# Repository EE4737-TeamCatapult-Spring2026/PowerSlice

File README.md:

# PowerSlice
The slice that does the power stuff

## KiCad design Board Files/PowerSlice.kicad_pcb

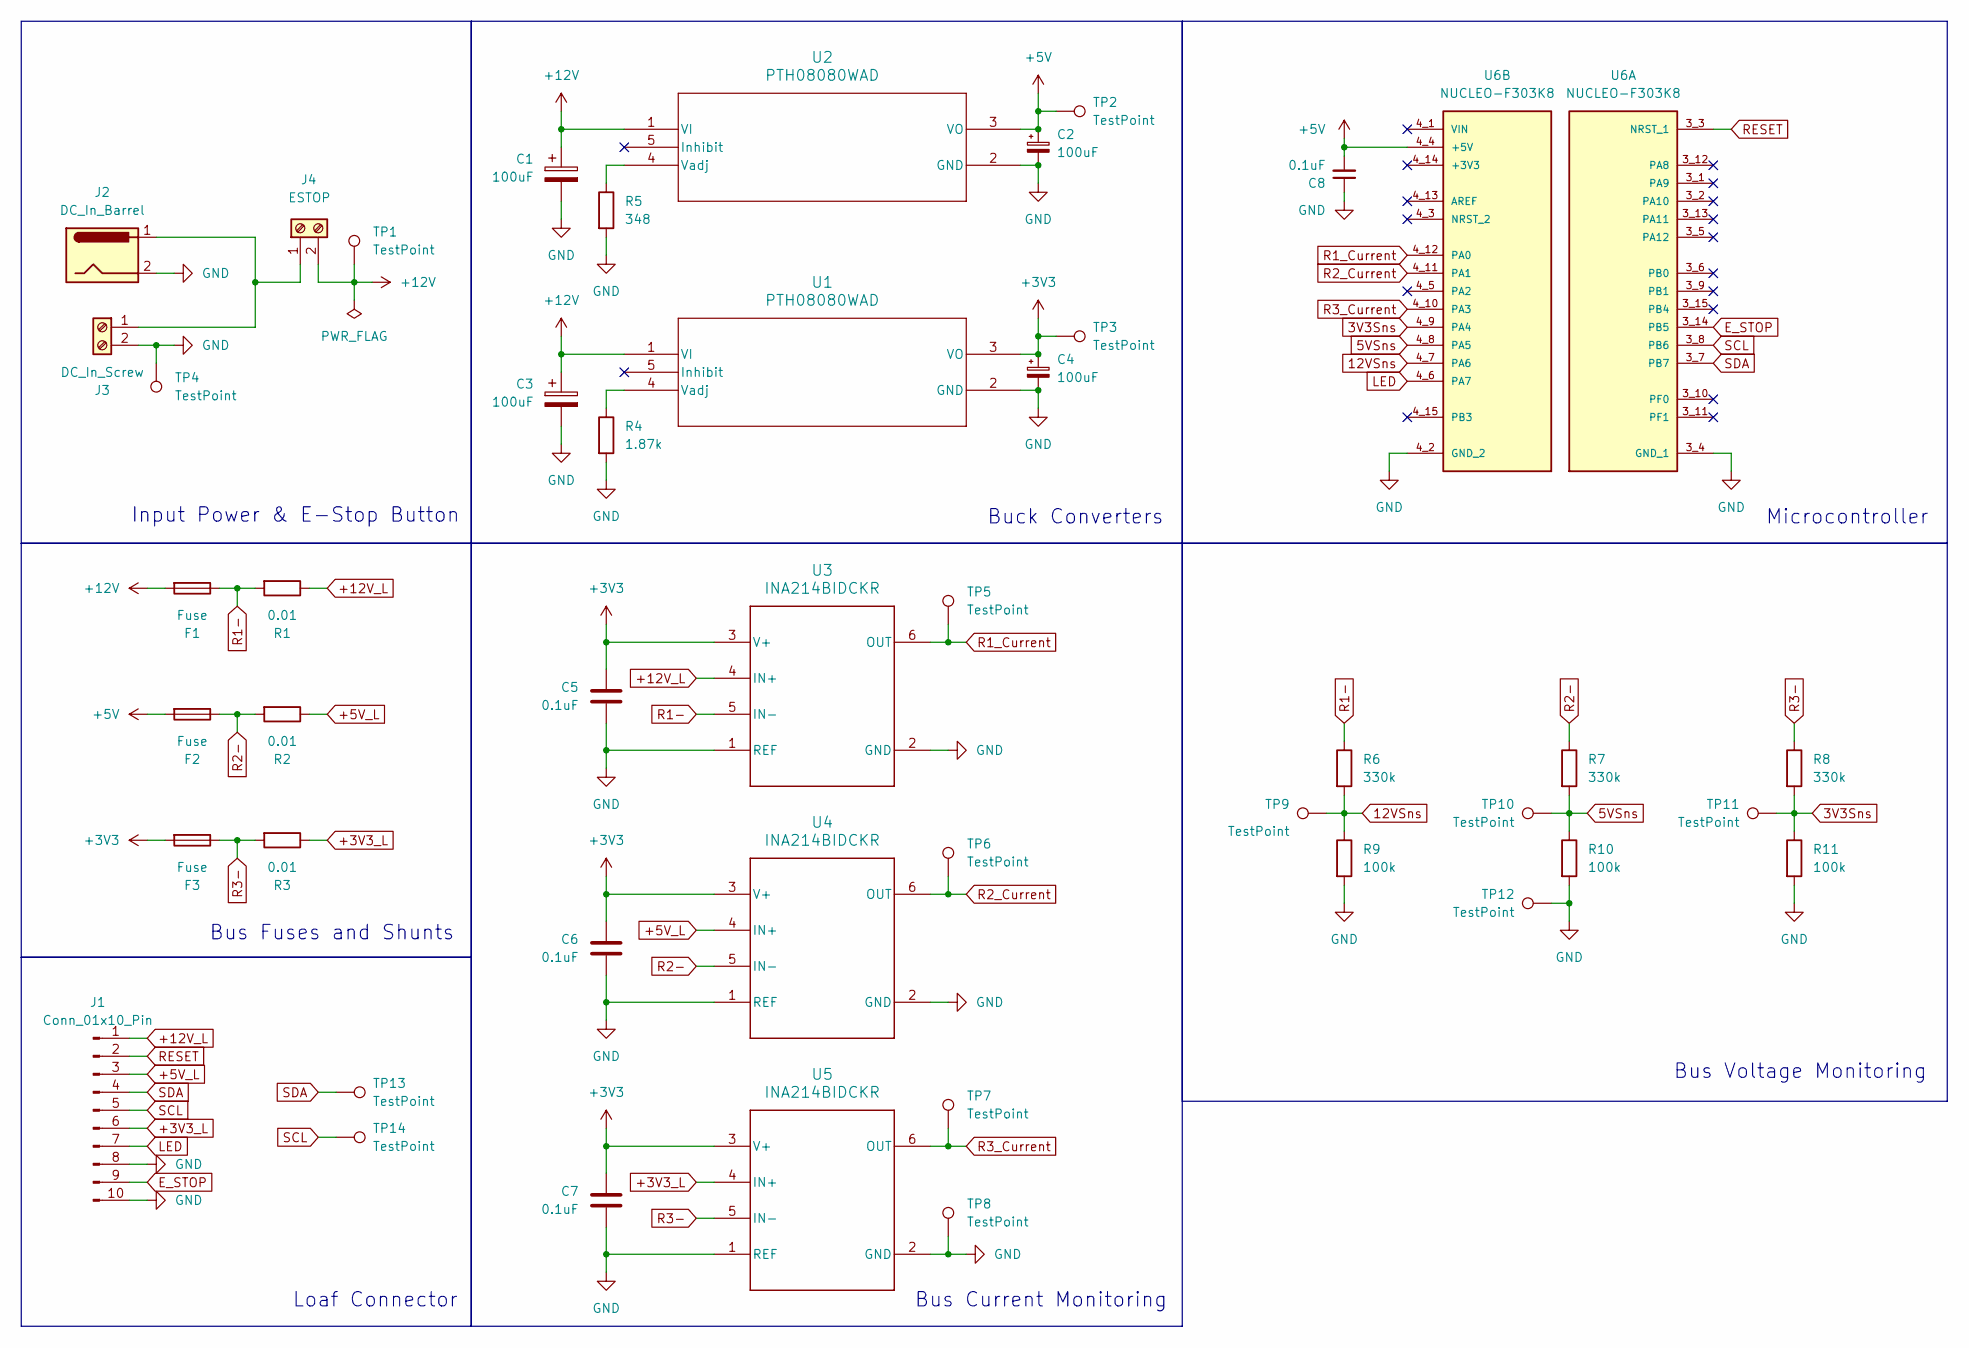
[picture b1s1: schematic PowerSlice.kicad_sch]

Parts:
C1, C2, C3, C4: 100uF; CP_Radial_D6.3mm_P2.50mm
C5, C6, C7, C8: 0.1uF; C_1206_3216Metric_Pad1.33x1.80mm_HandSolder
F1, F2, F3: Fuse; FUSE_354 101-GY_LTF
J1: Conn_01x10_Pin; PinHeader_1x10_P2.54mm_Horizontal
J2: DC_In_Barrel
J3: DC_In_Screw; 691137710002
J4: ESTOP; 691137710002
R1, R2, R3: 0.01; R_1206_3216Metric_Pad1.30x1.75mm_HandSolder
R4: 1.87k; R_1206_3216Metric_Pad1.30x1.75mm_HandSolder
R5: 348; R_1206_3216Metric_Pad1.30x1.75mm_HandSolder
R6, R7, R8: 330k; R_1206_3216Metric_Pad1.30x1.75mm_HandSolder
R9, R10, R11: 100k; R_1206_3216Metric_Pad1.30x1.75mm_HandSolder
TP1, TP2, TP3, TP4, TP5, TP6, TP7, TP8, TP9, TP10, TP11, TP12, TP13, TP14: TestPoint; TestPoint_Keystone_5005-5009_Compact
U1, U2: PTH08080WAD; EUF5
U3, U4, U5: INA214BIDCKR; DCK0006A_N
U6: NUCLEO-F303K8; MODULE_NUCLEO-F303K8; PARTREV 5

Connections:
3V3Sns: R8.2, R11.1, TP11.1 (1_1), U6.4_9 (PA4)
5VSns: R7.2, R10.1, TP10.1 (1_1), U6.4_8 (PA5)
12VSns: R6.2, R9.1, TP9.1 (1_1), U6.4_7 (PA6)
+3V3: C4.1, C5.1, C6.1, C7.1, F3.2, TP3.1 (1_1), U1.3 (VO), U3.3 (V+), U4.3 (V+), U5.3 (V+)
+3V3_L: J1.6, R3.1, U5.4 (IN+)
+5V: C2.1, C8.2, F2.2, TP2.1 (1_1), U2.3 (VO), U6.4_4 (+5V)
+5V_L: J1.3, R2.1, U4.4 (IN+)
+12V: C1.1, C3.1, F1.2, J4.2, TP1.1 (1_1), U1.1 (VI), U2.1 (VI)
+12V_L: J1.1, R1.1, U3.4 (IN+)
E_STOP: J1.9, U6.3_14 (PB5)
GND: C1.2, C2.2, C3.2, C4.2, C5.2, C6.2, C7.2, C8.1, J1.8, J1.10, J2.2, J3.2, R4.2, R5.2, R9.2, R10.2, R11.2, TP4.1 (1_1), TP8.1 (1_1), TP12.1 (1_1), U1.2 (GND), U2.2 (GND), U3.1 (REF), U3.2 (GND), U4.1 (REF), U4.2 (GND), U5.1 (REF), U5.2 (GND), U6.3_4 (GND_1), U6.4_2 (GND_2)
LED: J1.7, U6.4_6 (PA7)
unnamed: J2.1, J3.1, J4.1
unnamed: R4.1, U1.4 (Vadj)
unnamed: R5.1, U2.4 (Vadj)
R1-: F1.1, R1.2, R6.1, U3.5 (IN-)
R1_Current: TP5.1 (1_1), U3.6 (OUT), U6.4_12 (PA0)
R2-: F2.1, R2.2, R7.1, U4.5 (IN-)
R2_Current: TP6.1 (1_1), U4.6 (OUT), U6.4_11 (PA1)
R3-: F3.1, R3.2, R8.1, U5.5 (IN-)
R3_Current: TP7.1 (1_1), U5.6 (OUT), U6.4_10 (PA3)
RESET: J1.2, U6.3_3 (NRST_1)
SCL: J1.5, TP14.1 (1_1), U6.3_8 (PB6)
SDA: J1.4, TP13.1 (1_1), U6.3_7 (PB7)

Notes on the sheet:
Microcontroller
Bus Fuses and Shunts
Input Power & E-Stop Button
Bus Voltage Monitoring
Bus Current Monitoring
Loaf Connector
Buck Converters

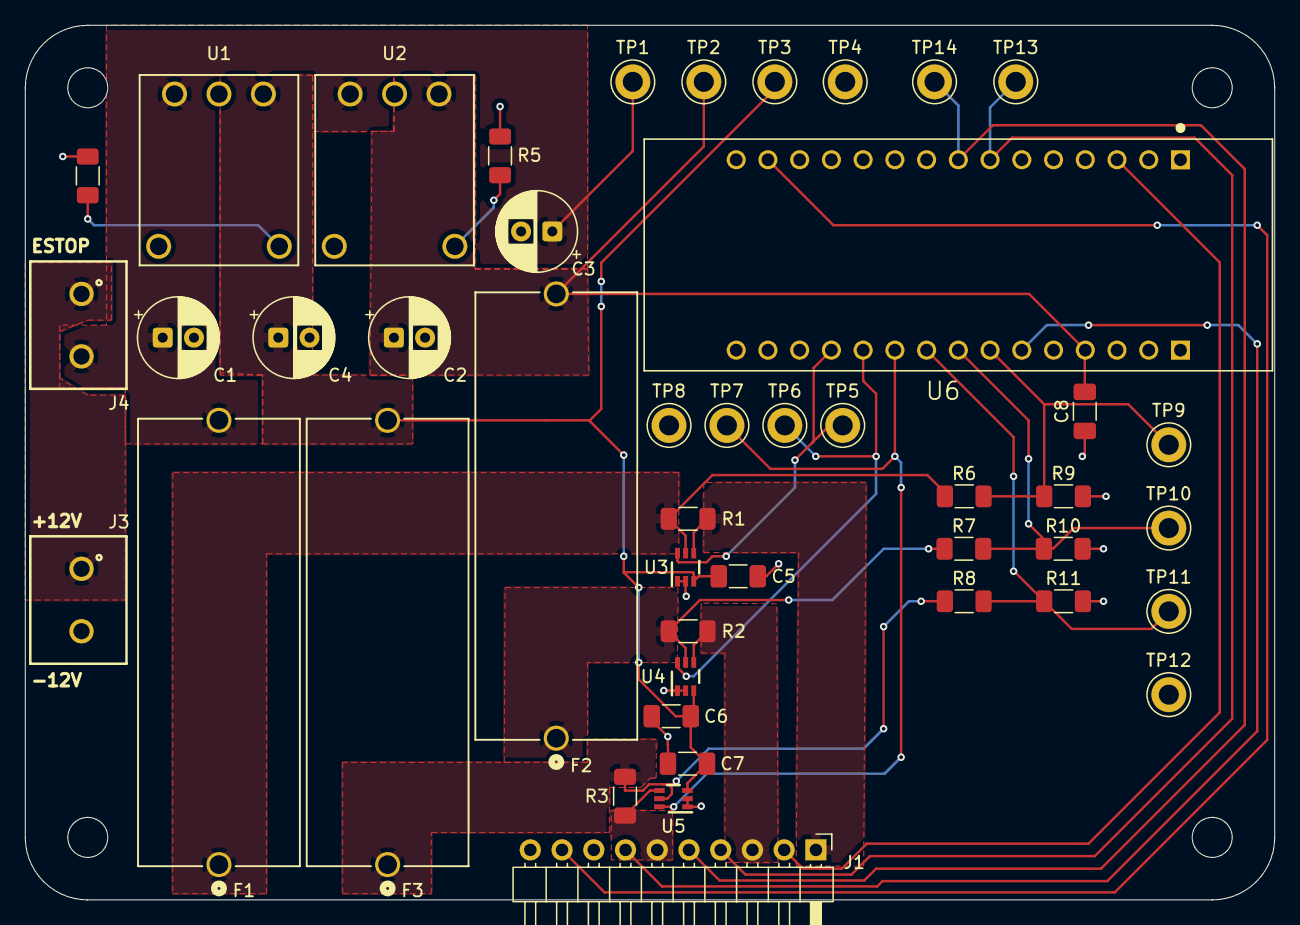
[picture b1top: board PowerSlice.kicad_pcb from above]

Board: 2 copper layers, 100.0 x 70.0 mm, 45 parts (0 on the bottom side), 24 nets.

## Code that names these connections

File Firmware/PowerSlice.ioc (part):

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Mcu.Name=STM32F303K(6-8)Tx
Mcu.Package=LQFP32
Mcu.UserName=STM32F303K8Tx
PA0.Mode=IN1-Single-Ended
PA0.Signal=ADC1_IN1
PA1.Mode=IN2-Single-Ended
PA1.Signal=ADC1_IN2
PA13.GPIOParameters=GPIO_Label
PA13.GPIO_Label=SWDIO
PA13.Mode=Serial_Wire
PA13.Signal=SYS_JTMS-SWDIO
PA14.GPIOParameters=GPIO_Label
PA14.GPIO_Label=SWCLK
PA14.Mode=Serial_Wire
PA14.Signal=SYS_JTCK-SWCLK
PA3.Mode=IN4-Single-Ended
PA3.Signal=ADC1_IN4
PA4.Mode=IN1-Single-Ended
PA4.Signal=ADC2_IN1
PA5.Mode=IN2-Single-Ended
PA5.Signal=ADC2_IN2
PA6.Mode=IN3-Single-Ended
PA6.Signal=ADC2_IN3
PA7.Signal=GPIO_Output
PB5.Signal=GPXTI5
PB6.Mode=I2C
PB6.Signal=I2C1_SCL
PB7.Mode=I2C
PB7.Signal=I2C1_SDA
PF0\ /\ OSC_IN.GPIOParameters=GPIO_Label
PF0\ /\ OSC_IN.GPIO_Label=MCO
PF0\ /\ OSC_IN.Mode=HSE-External-Clock-Source
PF0\ /\ OSC_IN.Signal=RCC_OSC_IN
RCC.HSEPLLFreq_Value=8000000
RCC.HSE_VALUE=8000000
RCC.SYSCLKFreq_VALUE=8000000
board=NUCLEO-F303K8
boardIOC=true

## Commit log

2026-01-21 started schematic work on power slice. TODO: MCU connections, loaf voltage dividers to measure loaf voltages safely on mcu
2026-01-27 finished preliminary schematic
2026-01-27 fixed all ERC warnings/errors
2026-02-09 updated some small pieces, namely estop is changed from a button symbol to a screw terminal for external connection
2026-02-17 Updated schematic + built PCB
2026-02-17 updated lightly after PCB review TODO: figure out LED and Header pins
2026-02-24 Wacky stuff that needs to be changed cuz it wont work and will be reverted
2026-02-24 Work, TODO: figure out external power connectors
2026-02-25 "Final" edits before submission for ordering
2026-03-17 Adding Firmware folder + renamed board files folder
2026-03-17 Added firmware project
2026-03-17 Setup base stm32 project
2026-03-24 Lab 11 Progress
    Added DMA ADC requests to process current data, starting to set up conditions for I2C communication
2026-04-07 Fixed voltage ADC reading problem :)
    ADCs work now, need to work on current sensing validation + I2C packet communication (ez)
2026-04-10 updated gitignore for KiCad 10
2026-04-10 Updated to KiCAD 10, fancified schematic for final presentation, verified ERC and DRC still good
2026-04-14 Update 4/14
2026-04-16 Updated I2C code
2026-04-19 firmware
2026-04-20 I2C WORKING
    yayayayayay
2026-06-04 final code push + cleaned up build directories
